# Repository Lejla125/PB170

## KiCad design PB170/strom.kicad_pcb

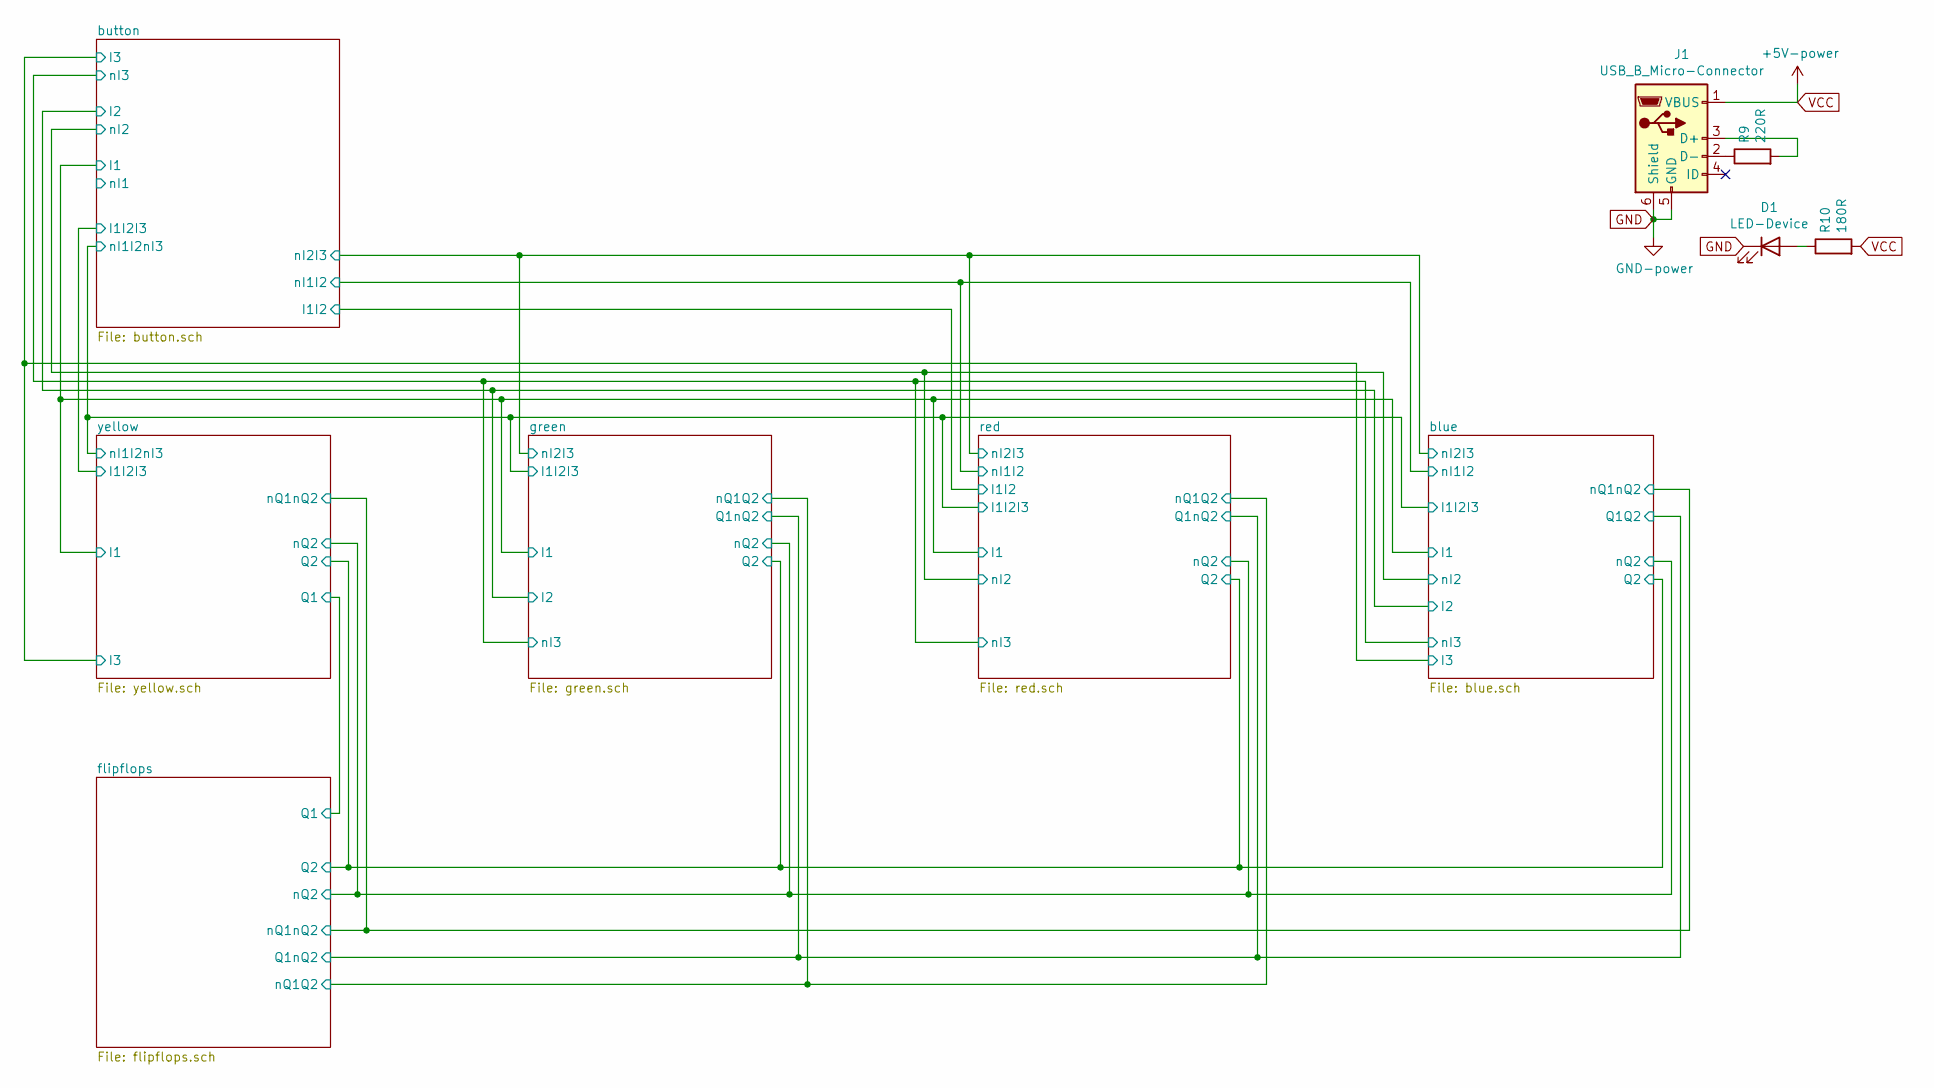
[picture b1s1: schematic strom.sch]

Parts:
D1: LED-Device; LED0603-R-RD; LCSC C34499
J1: USB_B_Micro-Connector; MICRO-USB-SMD_MICROXNJ; LCSC C404969
R9: 220R; R0603; LCSC C22962
R10: 180R; R0603; LCSC C22828

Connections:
GND: D1.1 (K), J1.5 (GND), J1.6 (Shield); also elsewhere on the board
unnamed: D1.2 (A), R10.1
unnamed: J1.2 (D-), R9.1
unnamed: J1.3 (D+), R9.2
VCC: J1.1 (VBUS), R10.2; also elsewhere on the board

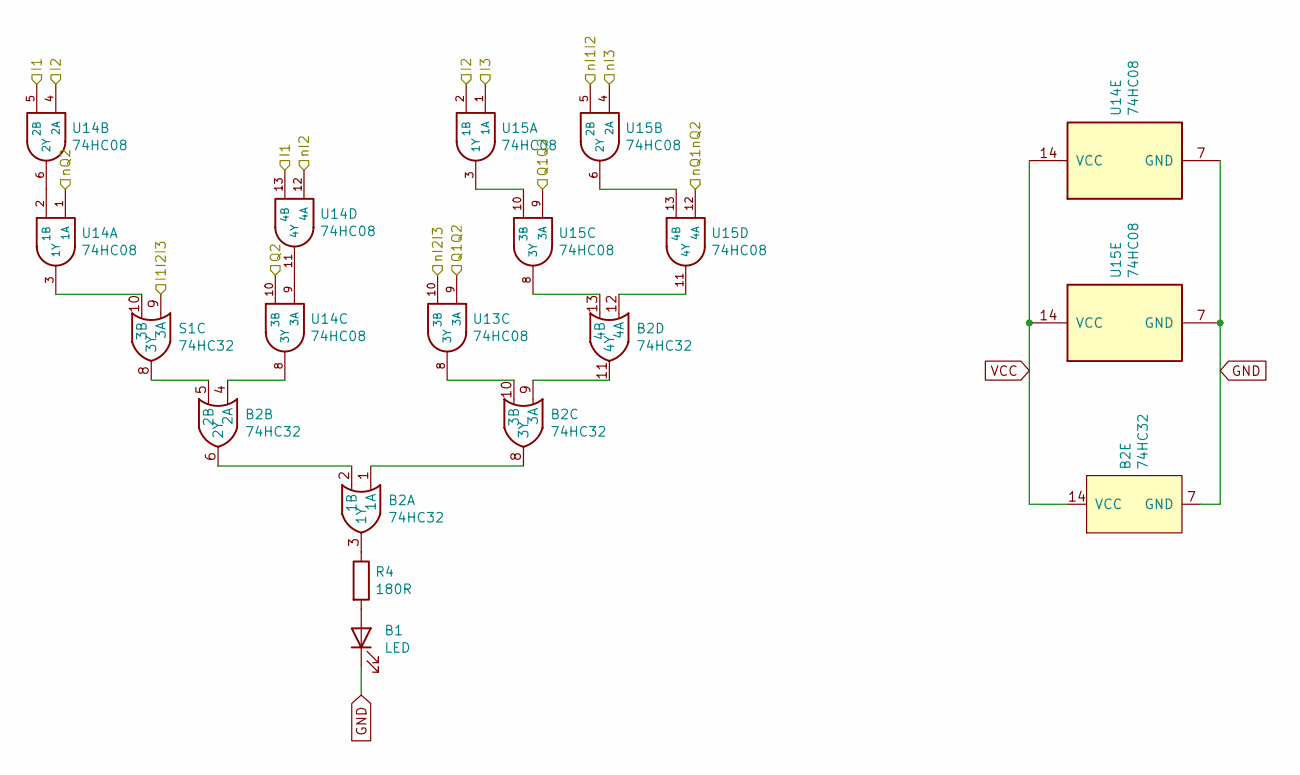
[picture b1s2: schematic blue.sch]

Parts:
B1: LED; LED0603-R-RD; LCSC C72041
B2: 74HC32; SOIC-14_L8.7-W3.9-P1.27-LS6.0-BL; LCSC C5632
R4: 180R; R0603; LCSC C22828
S1: 74HC32; SOIC-14_L8.7-W3.9-P1.27-LS6.0-BL; LCSC C5632
U13, U14, U15: 74HC08; SOIC-14_L8.7-W3.9-P1.27-LS6.0-BL; LCSC C5593

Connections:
/blue/I1: U14.5 (2B), U14.13 (4B); also elsewhere on the board
/blue/I1I2I3: S1.9 (3A); also elsewhere on the board
/blue/I2: U14.4 (2A), U15.2 (1B); also elsewhere on the board
/blue/I3: U15.1 (1A); also elsewhere on the board
/blue/Q1Q2: U13.9 (3A), U15.9 (3A); also elsewhere on the board
/blue/Q2: U14.10 (3B); also elsewhere on the board
/blue/nI1I2: U15.5 (2B); also elsewhere on the board
/blue/nI2: U14.12 (4A); also elsewhere on the board
/blue/nI2I3: U13.10 (3B); also elsewhere on the board
/blue/nI3: U15.4 (2A); also elsewhere on the board
/blue/nQ1nQ2: U15.12 (4A); also elsewhere on the board
/blue/nQ2: U14.1 (1A); also elsewhere on the board
GND: B1.1 (K), B2.7 (GND), U14.7 (GND), U15.7 (GND); also elsewhere on the board
unnamed: B1.2 (A), R4.2
unnamed: B2.1 (1A), B2.8 (3Y)
unnamed: B2.2 (1B), B2.6 (2Y)
unnamed: B2.3 (1Y), R4.1
unnamed: B2.4 (2A), U14.8 (3Y)
unnamed: B2.5 (2B), S1.8 (3Y)
unnamed: B2.10 (3B), U13.8 (3Y)
unnamed: B2.9 (3A), B2.11 (4Y)
unnamed: B2.12 (4A), U15.11 (4Y)
unnamed: B2.13 (4B), U15.8 (3Y)
unnamed: S1.10 (3B), U14.3 (1Y)
unnamed: U14.2 (1B), U14.6 (2Y)
unnamed: U14.9 (3A), U14.11 (4Y)
unnamed: U15.3 (1Y), U15.10 (3B)
unnamed: U15.6 (2Y), U15.13 (4B)
VCC: B2.14 (VCC), U14.14 (VCC), U15.14 (VCC); also elsewhere on the board

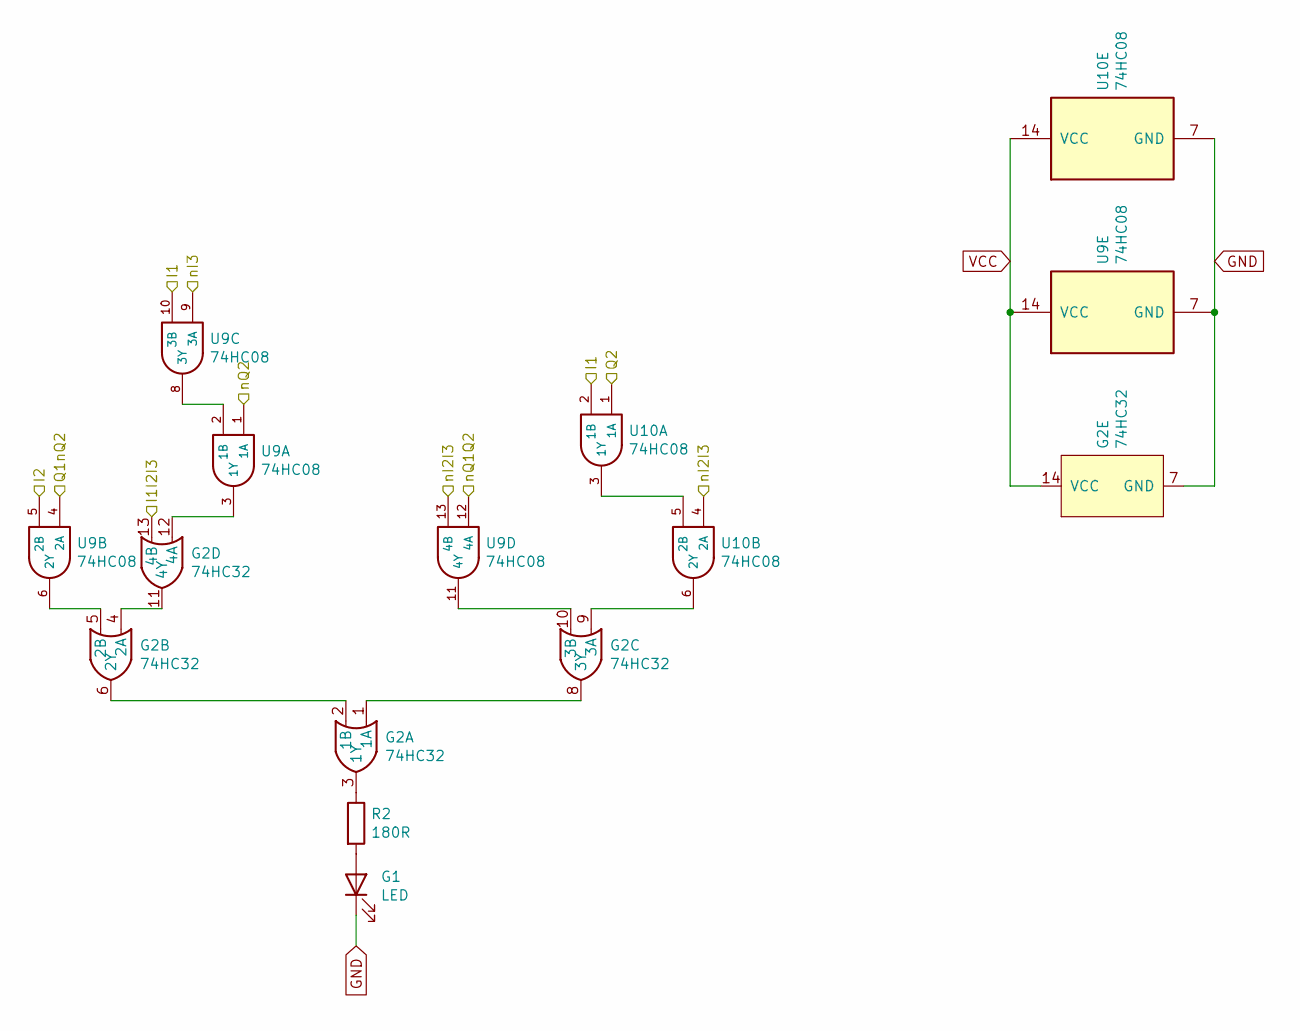
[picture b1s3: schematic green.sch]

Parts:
G1: LED; LED0603-R-RD; LCSC C72043
G2: 74HC32; SOIC-14_L8.7-W3.9-P1.27-LS6.0-BL; LCSC C5632
R2: 180R; R0603; LCSC C22828
U9, U10: 74HC08; SOIC-14_L8.7-W3.9-P1.27-LS6.0-BL; LCSC C5593

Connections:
/blue/I1: U9.10 (3B), U10.2 (1B); also elsewhere on the board
/blue/I1I2I3: G2.13 (4B); also elsewhere on the board
/blue/I2: U9.5 (2B); also elsewhere on the board
/blue/Q1Q2: U9.4 (2A); also elsewhere on the board
/blue/Q2: U10.1 (1A); also elsewhere on the board
/blue/nI2I3: U9.13 (4B), U10.4 (2A); also elsewhere on the board
/blue/nI3: U9.9 (3A); also elsewhere on the board
/blue/nQ2: U9.1 (1A); also elsewhere on the board
/flipflops/nQ1Q2: U9.12 (4A); also elsewhere on the board
GND: G1.1 (K), G2.7 (GND), U9.7 (GND), U10.7 (GND); also elsewhere on the board
unnamed: G1.2 (A), R2.2
unnamed: G2.1 (1A), G2.8 (3Y)
unnamed: G2.2 (1B), G2.6 (2Y)
unnamed: G2.3 (1Y), R2.1
unnamed: G2.5 (2B), U9.6 (2Y)
unnamed: G2.9 (3A), U10.6 (2Y)
unnamed: G2.10 (3B), U9.11 (4Y)
unnamed: G2.4 (2A), G2.11 (4Y)
unnamed: G2.12 (4A), U9.3 (1Y)
unnamed: U9.2 (1B), U9.8 (3Y)
unnamed: U10.3 (1Y), U10.5 (2B)
VCC: G2.14 (VCC), U9.14 (VCC), U10.14 (VCC); also elsewhere on the board

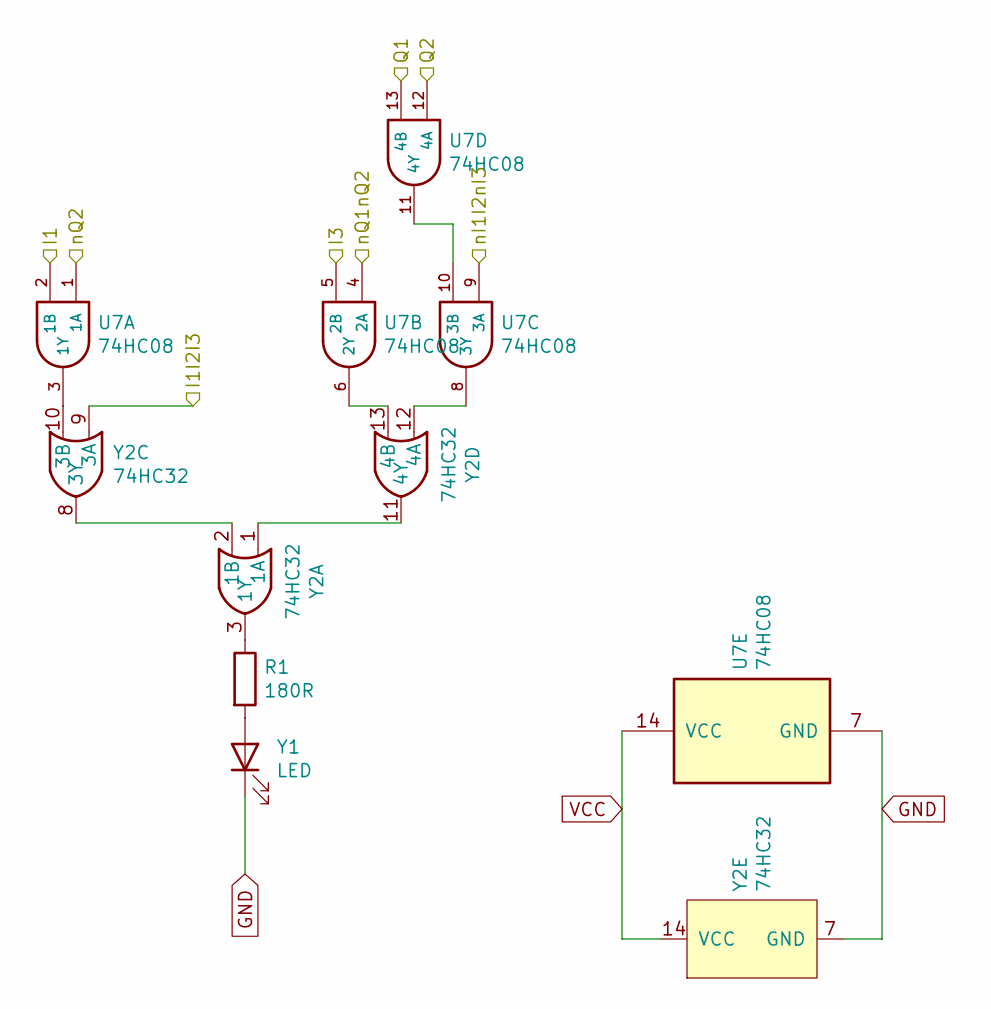
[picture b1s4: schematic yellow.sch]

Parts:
R1: 180R; R0603; LCSC C22828
U7: 74HC08; SOIC-14_L8.7-W3.9-P1.27-LS6.0-BL; LCSC C5593
Y1: LED; LED0603-R-RD; LCSC C72038
Y2: 74HC32; SOIC-14_L8.7-W3.9-P1.27-LS6.0-BL; LCSC C5632

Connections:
/blue/I1: U7.2 (1B); also elsewhere on the board
/blue/I1I2I3: U7.9 (3A); also elsewhere on the board
/blue/I3: U7.5 (2B); also elsewhere on the board
/blue/Q2: U7.12 (4A); also elsewhere on the board
/blue/nQ1nQ2: U7.4 (2A); also elsewhere on the board
/blue/nQ2: U7.1 (1A); also elsewhere on the board
/button/I1I2I3: Y2.9 (3A); also elsewhere on the board
/flipflops/Q1: U7.13 (4B); also elsewhere on the board
GND: U7.7 (GND), Y1.1 (K), Y2.7 (GND); also elsewhere on the board
unnamed: R1.1, Y2.3 (1Y)
unnamed: R1.2, Y1.2 (A)
unnamed: U7.3 (1Y), Y2.10 (3B)
unnamed: U7.6 (2Y), Y2.13 (4B)
unnamed: U7.8 (3Y), Y2.12 (4A)
unnamed: U7.10 (3B), U7.11 (4Y)
unnamed: Y2.1 (1A), Y2.11 (4Y)
unnamed: Y2.2 (1B), Y2.8 (3Y)
VCC: U7.14 (VCC), Y2.14 (VCC); also elsewhere on the board

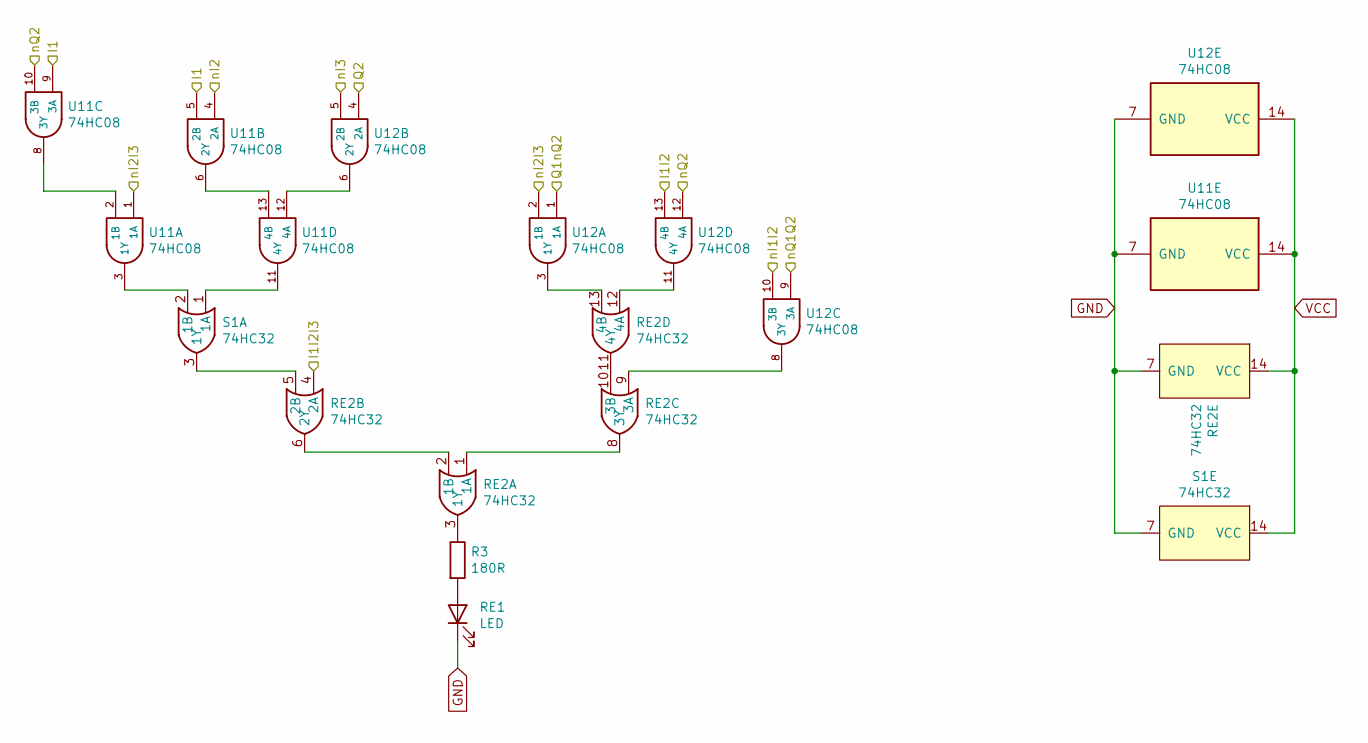
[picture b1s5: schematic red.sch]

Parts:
R3: 180R; R0603; LCSC C22828
RE1: LED; LED0603-R-RD; LCSC C2286
RE2: 74HC32; SOIC-14_L8.7-W3.9-P1.27-LS6.0-BL; LCSC C5632
S1: 74HC32; SOIC-14_L8.7-W3.9-P1.27-LS6.0-BL; LCSC C5632
U11, U12: 74HC08; SOIC-14_L8.7-W3.9-P1.27-LS6.0-BL; LCSC C5593

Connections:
/blue/I1: U11.5 (2B), U11.9 (3A); also elsewhere on the board
/blue/I1I2I3: RE2.4 (2A); also elsewhere on the board
/blue/Q1Q2: U12.1 (1A); also elsewhere on the board
/blue/Q2: U12.4 (2A); also elsewhere on the board
/blue/nI1I2: U12.10 (3B); also elsewhere on the board
/blue/nI2: U11.4 (2A); also elsewhere on the board
/blue/nI2I3: U11.1 (1A), U12.2 (1B); also elsewhere on the board
/blue/nI3: U12.5 (2B); also elsewhere on the board
/blue/nQ2: U11.10 (3B), U12.12 (4A); also elsewhere on the board
/button/I1I2: U12.13 (4B); also elsewhere on the board
/flipflops/nQ1Q2: U12.9 (3A); also elsewhere on the board
GND: RE1.1 (K), RE2.7 (GND), S1.7 (GND), U11.7 (GND), U12.7 (GND); also elsewhere on the board
unnamed: R3.1, RE2.3 (1Y)
unnamed: R3.2, RE1.2 (A)
unnamed: RE2.1 (1A), RE2.8 (3Y)
unnamed: RE2.2 (1B), RE2.6 (2Y)
unnamed: RE2.5 (2B), S1.3 (1Y)
unnamed: RE2.9 (3A), U12.8 (3Y)
unnamed: RE2.10 (3B), RE2.11 (4Y)
unnamed: RE2.12 (4A), U12.11 (4Y)
unnamed: RE2.13 (4B), U12.3 (1Y)
unnamed: S1.1 (1A), U11.11 (4Y)
unnamed: S1.2 (1B), U11.3 (1Y)
unnamed: U11.2 (1B), U11.8 (3Y)
unnamed: U11.12 (4A), U12.6 (2Y)
unnamed: U11.6 (2Y), U11.13 (4B)
VCC: RE2.14 (VCC), S1.14 (VCC), U11.14 (VCC), U12.14 (VCC); also elsewhere on the board

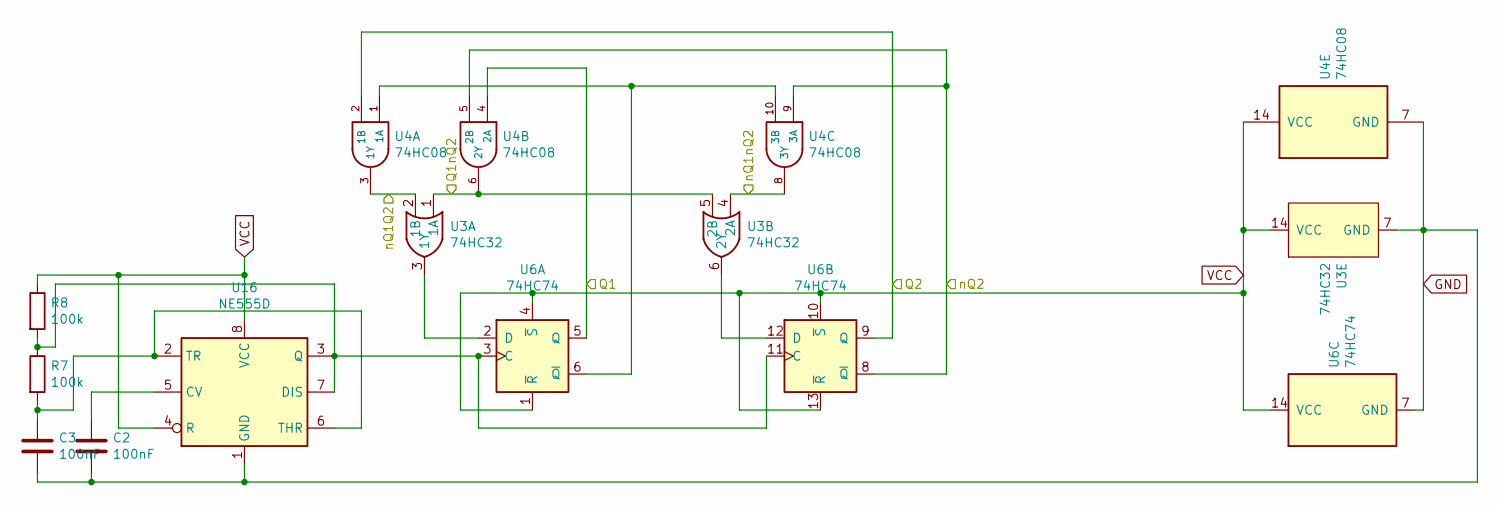
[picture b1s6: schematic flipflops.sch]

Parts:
C2, C3: 100nF; C0603; LCSC C14663
R7, R8: 100k; R0603; LCSC C21190
U3: 74HC32; TSSOP-14_L5.0-W4.4-P0.65-LS6.4-BL; LCSC C5632
U4: 74HC08; SOIC-14_L8.7-W3.9-P1.27-LS6.0-BL; LCSC C5593
U6: 74HC74; TSSOP-14_L5.0-W4.4-P0.65-LS6.4-BL; LCSC C6761
U16: NE555D; SOIC-8_L4.9-W3.9-P1.27-LS6.0-BL; LCSC C7593

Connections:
/blue/Q1Q2: U3.1 (1A), U3.5 (2B), U4.6 (2Y); also elsewhere on the board
/blue/Q2: U4.2 (1B), U6.9 (Q); also elsewhere on the board
/blue/nQ1nQ2: U3.4 (2A), U4.8 (3Y); also elsewhere on the board
/blue/nQ2: U4.5 (2B), U4.9 (3A), U6.8 (~Q); also elsewhere on the board
/flipflops/Q1: U4.4 (2A), U6.5 (Q); also elsewhere on the board
/flipflops/nQ1Q2: U3.2 (1B), U4.3 (1Y); also elsewhere on the board
GND: C2.2, C3.2, U3.7 (GND), U4.7 (GND), U6.7 (GND), U16.1 (GND); also elsewhere on the board
unnamed: C2.1, U16.5 (CV)
unnamed: C3.1, R7.2, U16.2 (TR), U16.6 (THR)
unnamed: R7.1, R8.2, U6.3 (C), U6.11 (C), U16.3 (Q), U16.7 (DIS)
unnamed: U3.3 (1Y), U6.2 (D)
unnamed: U3.6 (2Y), U6.12 (D)
unnamed: U4.1 (1A), U4.10 (3B), U6.6 (~Q)
VCC: R8.1, U3.14 (VCC), U4.14 (VCC), U6.1 (~R), U6.4 (~S), U6.10 (~S), U6.13 (~R), U6.14 (VCC), U16.4 (R), U16.8 (VCC); also elsewhere on the board

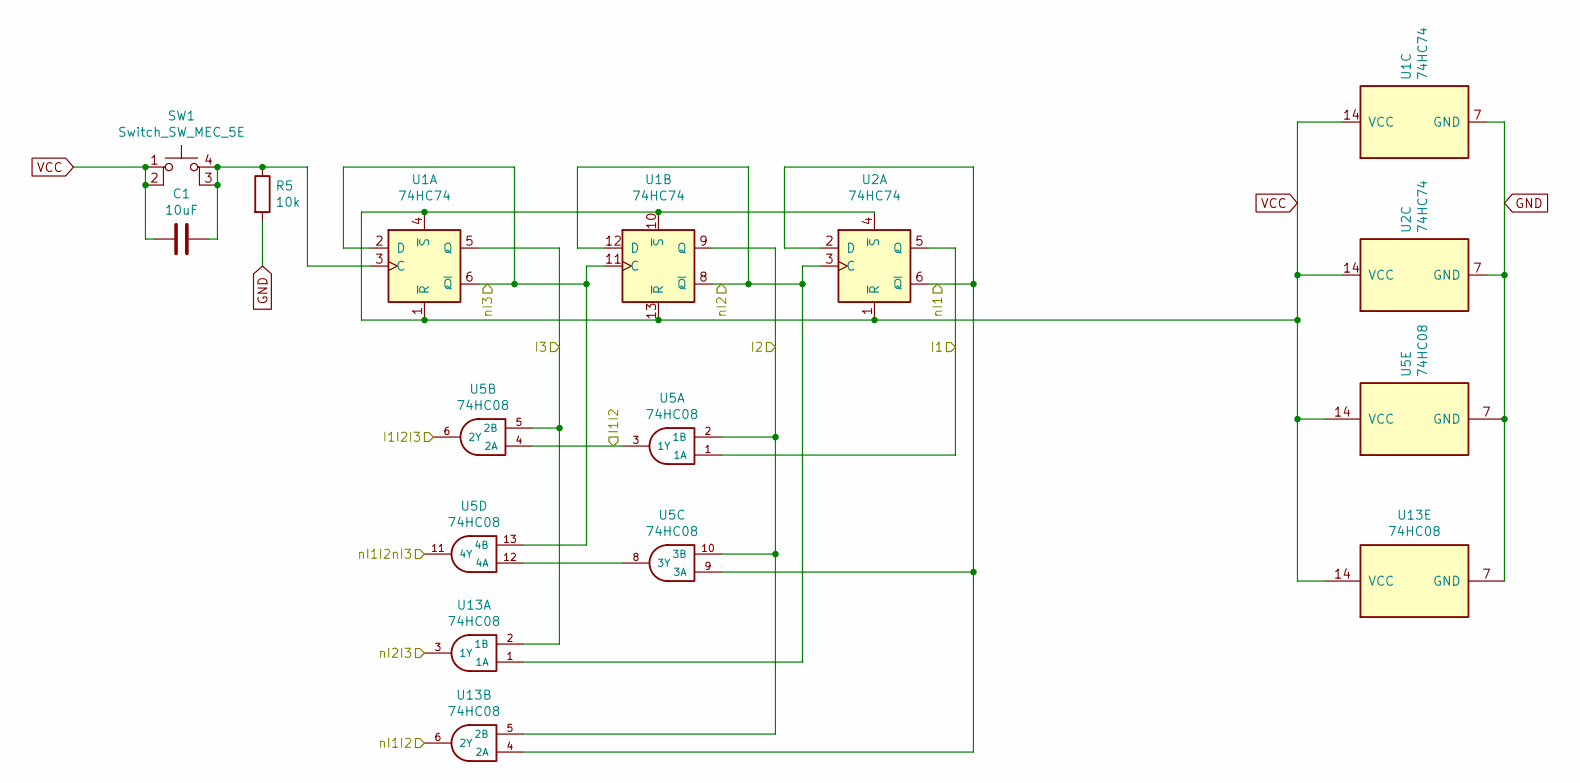
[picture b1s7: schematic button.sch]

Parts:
C1: 10uF; C0603; LCSC C19702
R5: 10k; R0603; LCSC C25804
SW1: Switch_SW_MEC_5E; TactileSwitch_C381064; LCSC C381064
U1, U2: 74HC74; TSSOP-14_L5.0-W4.4-P0.65-LS6.4-BL; LCSC C6761
U5, U13: 74HC08; SOIC-14_L8.7-W3.9-P1.27-LS6.0-BL; LCSC C5593

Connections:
/blue/I1: U2.5 (Q), U5.1 (1A); also elsewhere on the board
/blue/I1I2I3: U5.11 (4Y); also elsewhere on the board
/blue/I2: U1.9 (Q), U5.2 (1B), U5.10 (3B), U13.5 (2B); also elsewhere on the board
/blue/I3: U1.5 (Q), U5.5 (2B), U13.2 (1B); also elsewhere on the board
/blue/nI1I2: U13.6 (2Y); also elsewhere on the board
/blue/nI2: U1.8 (~Q), U1.12 (D), U2.3 (C), U13.1 (1A); also elsewhere on the board
/blue/nI2I3: U13.3 (1Y); also elsewhere on the board
/blue/nI3: U1.2 (D), U1.6 (~Q), U1.11 (C), U5.13 (4B); also elsewhere on the board
/button/I1I2: U5.3 (1Y), U5.4 (2A); also elsewhere on the board
/button/I1I2I3: U5.6 (2Y); also elsewhere on the board
/button/nI1: U2.2 (D), U2.6 (~Q), U5.9 (3A), U13.4 (2A)
GND: R5.2, U1.7 (GND), U2.7 (GND), U5.7 (GND), U13.7 (GND); also elsewhere on the board
unnamed: C1.1, R5.1, SW1.3 (K), SW1.4 (A), U1.3 (C)
unnamed: U5.8 (3Y), U5.12 (4A)
VCC: C1.2, SW1.1, SW1.2, U1.1 (~R), U1.4 (~S), U1.10 (~S), U1.13 (~R), U1.14 (VCC), U2.1 (~R), U2.4 (~S), U2.14 (VCC), U5.14 (VCC), U13.14 (VCC); also elsewhere on the board

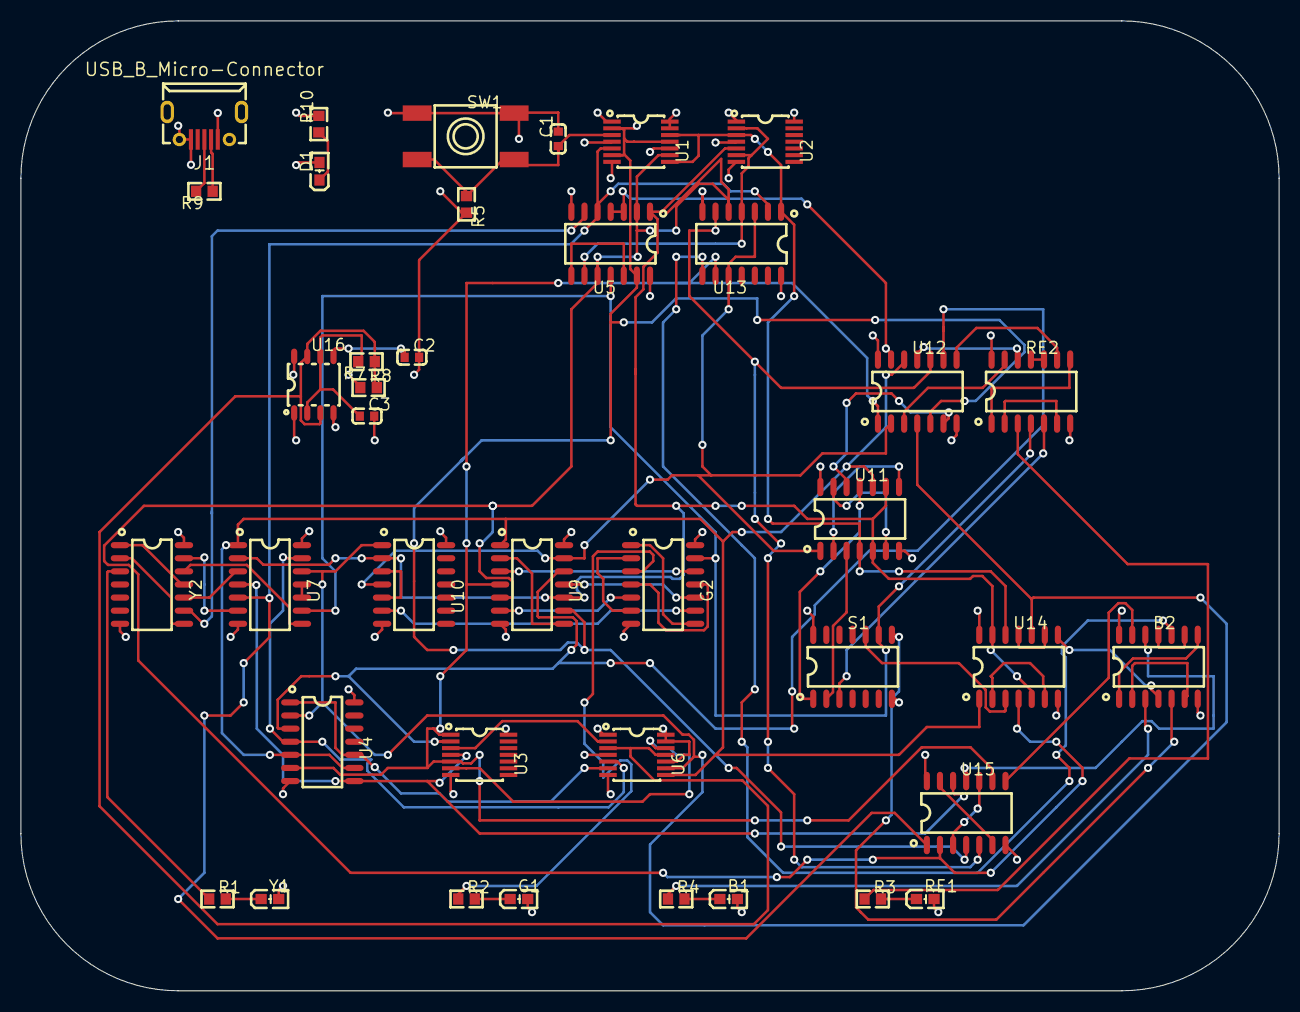
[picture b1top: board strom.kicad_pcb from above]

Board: 4 copper layers, 121.9 x 94.0 mm, 39 parts (0 on the bottom side), 78 nets.

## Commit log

2021-02-10 initial schema
2021-02-16 adding files
2021-02-17 changed USB position in PCB
2021-02-18 Changed button position
2021-02-18 Added documentation and user manual
2021-02-18 Documentation edited
